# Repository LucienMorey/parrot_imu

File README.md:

# parrot_imu

## Purpose

This design will host an IMU board for the Parody tripedal robotic platform. It will expose connect an IMU to the teensy 4.1 microcontroller with the ability to deliver this data over CAN bus and over an ethernet connection.

## TODOs

### Power Subsystem

Take a 24 V input and reduce it to supplies for powering the associated subsystems.

- [x] 5v supply - tentatitvely [VR10S05](https://www.digikey.com.au/en/products/detail/xp-power/VR10S05/13147713)
- [x] 3.3v supply - tentatitvely [TR05S3V3](https://www.digikey.com.au/en/products/detail/xp-power/TR05S3V3/4488636)
- [x] add terminal to supply power input. probably one of thosegreen terminals that can fit a ferule or a wago terminal [panel mount xt30](https://www.ebay.com.au/itm/393171351901)
- [x] Is it worth bothering with reverse polarity protection? Just a shottkey diode? Nope. just added a gendered connector to prevent this.
- [x] debugging LEDS to indicate presense of power
  - [x] at input line
  - [x] after 5v supply
  - [x] after 3.3V supply
- [x] calculate resitors for power leds

Q. what is an LDO and will it suffice or is a proper dc/dc converter required?

A. They both do the same thing with regard to switching direct current voltages. DC/DC converters are more efficent but more suspetable to noise because they use fets and things that generate switching noise. LDOS are less efficient and will have some current drop depending on the load drawn from the supply. An LDO will work in this scenario and they are cheaper so I will probably go for that. Tony recommended dcdc converter so switching

### Can Transeiver

One potential mechanism for delivering IMU data to the robot comms network. This is the back up option because it cannot interface directly to the ros network. It does not require FD functionality for higher bit rates but this option will be made available if a component can be sourced.

- [x] Pick a can trasniever that can interface with the teensy - picked the [TJA1441AT/0Z](https://www.digikey.com.au/en/products/detail/nxp-usa-inc/TJA1441AT-0Z/13691175). This shouldnt be an issue because it provides both 5v VCC and a seperate VIO input that I can specify the 3.3v logic level required for the teensy
- [x] create footprint and symbol
- [x] add optional termination points
- [x] Add a proper screw terminal or similar mechanism to make adding to the can bus easy [scrw terminal here](https://www.digikey.com.au/en/products/detail/cui-devices/TB005-762-02BE/10064113)
- [ ] Add proper Silk screen markers to indicate CAN-H/L so things are easy

### Ethernet Jack

Intended to be the primary mechanism for delivering imu data to the robot comms network. This is known to beable to interface directly with the ros network through microros on udp transports.

- [x] Find an approppriate RJ45 magjack connector - Currently the [SI-60062-F](https://www.digikey.com.au/en/products/detail/bel-fuse-inc/SI-60062-F/1033372)
- [x] Wire the connector to the teensy. note to follow the schematic outlined on thier magjack page found [here](https://www.pjrc.com/store/ethernet_kit.html). This should be as simple as just adding a capacitor and joining the pins but double check the smc design to be sure.
- [ ] Find link to small pins for ethernet

### Teensy 4.1

Primary microcontroller for interfacing with the IMU.

- [x] obtain premade footprint
- [ ] remember different pin styles for ethernet and general gpio
- [x] spi connection avoiding pin 13 so that ethernet can be used

### IMU

- [x] create symbol
- [x] create footprint
- [x] connect to SPI2 or 3 to avoid collision with ethernet
- [ ] Place footprint of breakout board
- [ ] double check if this should be i2c instead of spi
- [ ] check if interrupt pin or other functionality is going to be helpful

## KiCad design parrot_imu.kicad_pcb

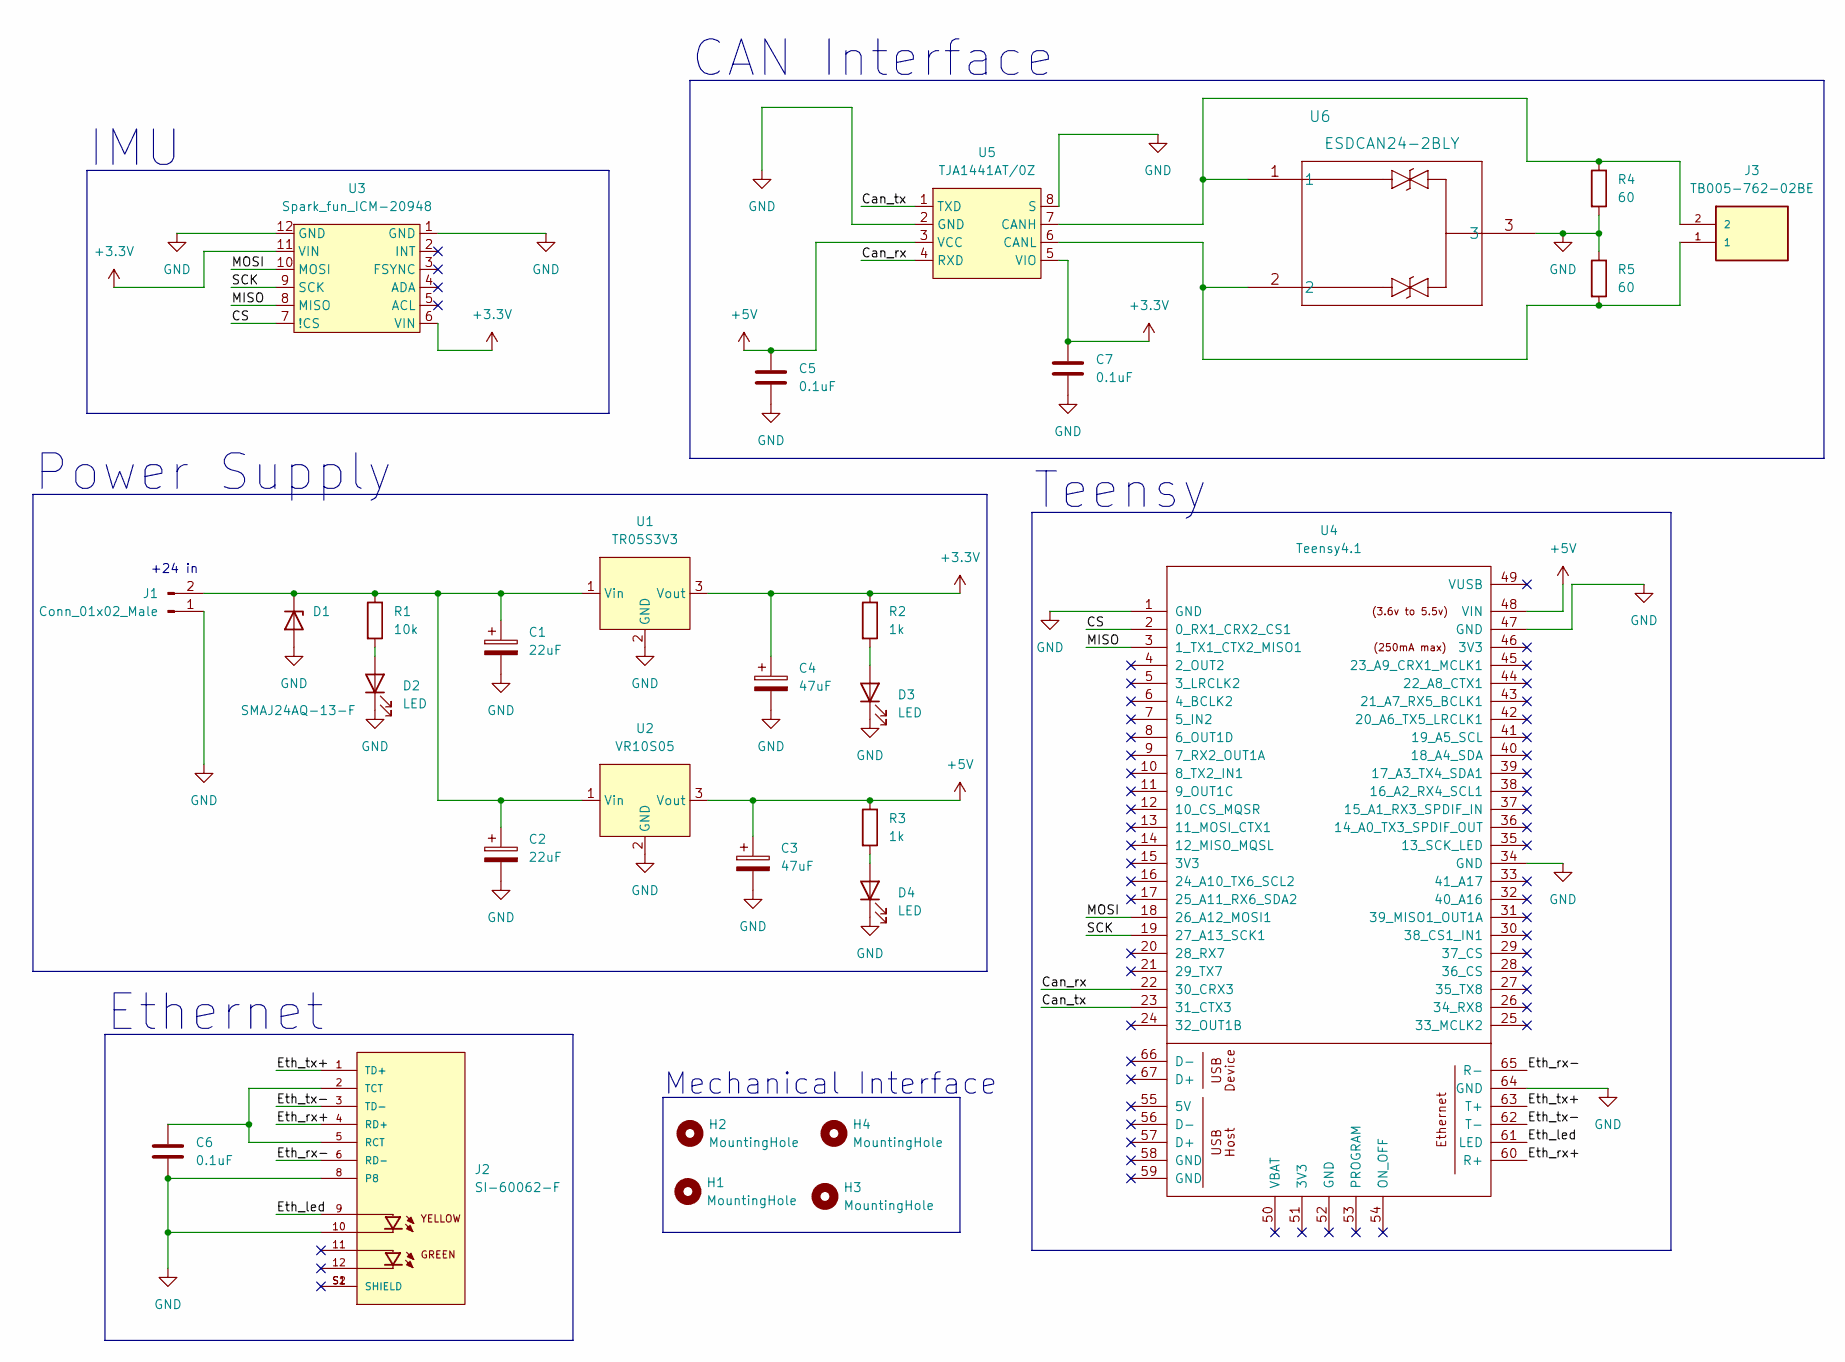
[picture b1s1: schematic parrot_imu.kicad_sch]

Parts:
C1, C2: 22uF; CP_Radial_D5.0mm_P2.00mm; Digikey 732-8857-1-ND
C3, C4: 47uF; CP_Radial_D6.3mm_P2.50mm; Digikey 732-8859-1-ND
C5, C6, C7: 0.1uF; C_0603_1608Metric; Digikey 1276-1935-1-ND
D1: SMAJ24AQ-13-F
D2, D3, D4: LED; LED_0603_1608Metric; Digikey 3147-B1911USD-20D000114U1930CT-ND
H1, H2, H3, H4: MountingHole; MountingHole_3.2mm_M3
J1: Conn_01x02_Male; AMASS_XT30PW-M_1x02_P2.50mm_Horizontal
J2: SI-60062-F; BEL_SI-60062-F; PARTREV B0
J3: TB005-762-02BE; CUI_TB005-762-02BE; Digikey 102-6189-ND
R1: 10k; R_0603_1608Metric; Digikey RNCP0603FTD10K0CT-ND
R2, R3: 1k; R_0603_1608Metric; Digikey RNCP0603FTD1K00CT-ND
R4, R5: 60; R_0603_1608Metric; Digikey 311-60.4HRCT-ND
U1: TR05S3V3; Digikey 1470-2257-5-ND
U2: VR10S05; Digikey 1470-VR10S05-ND
U3: Spark_fun_ICM-20948; Spark_fun_ICM-20498
U4: Teensy4.1; Teensy41
U5: TJA1441AT/0Z; SO-8_3.9x4.9mm_P1.27mm; Digikey 568-TJA1441AT/0ZCT-ND
U6: ESDCAN24-2BLY

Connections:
+3.3V: C4.1, C7.1, R2.1, U1.3 (Vout), U3.6 (VIN), U3.11 (VIN), U5.5 (VIO)
+5V: C3.1, C5.1, R3.1, U2.3 (Vout), U4.48 (VIN), U5.3 (VCC)
/CS: U3.7 (!CS), U4.2 (0_RX1_CRX2_CS1)
/Can_rx: U4.22 (30_CRX3), U5.4 (RXD)
/Can_tx: U4.23 (31_CTX3), U5.1 (TXD)
/Eth_led: J2.9, U4.61 (LED)
/Eth_rx+: J2.4 (RD+), U4.60 (R+)
/Eth_rx-: J2.6 (RD-), U4.65 (R-)
/Eth_tx+: J2.1 (TD+), U4.63 (T+)
/Eth_tx-: J2.3 (TD-), U4.62 (T-)
/MISO: U3.8 (MISO), U4.3 (1_TX1_CTX2_MISO1)
/MOSI: U3.10 (MOSI), U4.18 (26_A12_MOSI1)
/SCK: U3.9 (SCK), U4.19 (27_A13_SCK1)
GND: C1.2, C2.2, C3.2, C4.2, C5.2, C6.2, C7.2, D1.2 (A), D2.1 (K), D3.1 (K), D4.1 (K), J1.1, J2.8, J2.10, R4.2, R5.1, U1.2 (GND), U2.2 (GND), U3.1 (GND), U3.12 (GND), U4.1 (GND), U4.34 (GND), U4.47 (GND), U4.64 (GND), U5.2 (GND), U5.8 (S), U6.3
unnamed: C1.1, C2.1, D1.1 (K), J1.2, R1.1, U1.1 (Vin), U2.1 (Vin)
unnamed: C6.1, J2.2 (TCT), J2.5 (RCT)
unnamed: D2.2 (A), R1.2
unnamed: D3.2 (A), R2.2
unnamed: D4.2 (A), R3.2
unnamed: J3.1, R5.2, U5.6 (CANL), U6.2
unnamed: J3.2, R4.1, U5.7 (CANH), U6.1

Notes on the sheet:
Power Supply
CAN Interface
IMU
Mechanical Interface
Ethernet
Teensy
+24 in

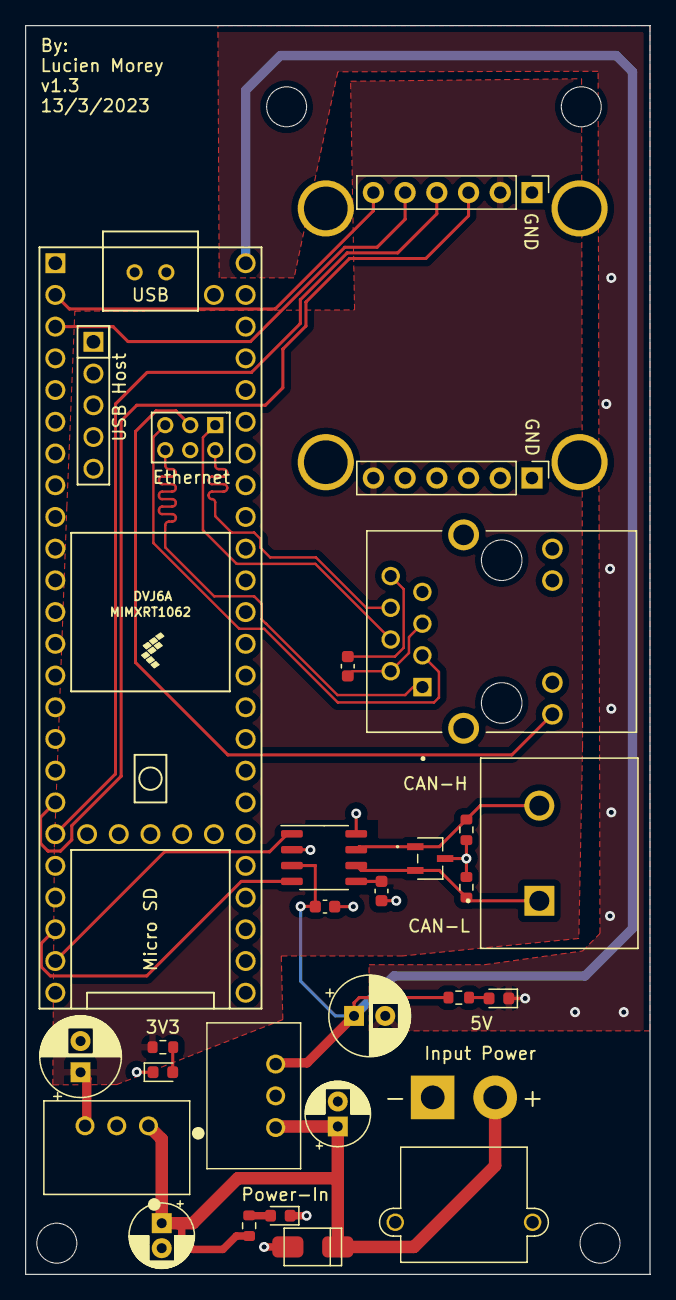
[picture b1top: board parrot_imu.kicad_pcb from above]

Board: 2 copper layers, 50.0 x 100.0 mm, 29 parts (0 on the bottom side), 21 nets.

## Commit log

2023-02-01 created basic kicad project
2023-02-01 added basic notes and todo list for project
2023-02-01 added libraries for teensy
2023-02-01 added teensy to schematic
2023-02-01 added backups folder to gitignore
2023-02-01 added ethernet jack symbol
2023-02-01 added digikey part number to ethernet part
2023-02-01 added readme notes about ethernet comms
2023-02-02 more notes on readme
2023-02-02 created footprint and symbol for ldo
2023-02-02 added additional todos and marked some things as complete
2023-02-03 created symbol and linked footprint for can transciever
2023-02-03 updates to README.md
2023-02-03 tweak to symbols and added imu breakout footprint/symbol
2023-02-03 added ics to schematic
2023-02-03 updates to todo list
2023-02-03 some progress on the schematic and notes on other things to handle
2023-02-06 added connector library
2023-02-06 dcdc supply footprints and symbols
2023-02-06 schematic done pre review
2023-02-06 added notes and digikey part numbers
2023-02-06 README updates
2023-02-06 design review with tony
2023-02-08 added tvs diodes to schematic
2023-02-08 switched to xt30 connector and added leds for power
2023-02-08 update to readme
2023-02-08 filled in footprints and digikey id for most parts
2023-02-08 readme update
2023-02-22 added missing footprint for can protection and imported parts to pcb design
2023-02-22 sort out errors with footprints and add mounting holes
2023-02-22 start of laying out components
2023-02-22 most of pcb and some steps
2023-02-22 completed draft pcb and added model for imu
2023-02-22 fix unconnected plane error
2023-02-22 fix errors with unconnected components
2023-02-23 removed trace between shield on ethernet
2023-02-23 dump of progress
2023-02-23 pcb redesign
2023-02-26 added step file for ethernet
2023-02-26 readded xt30 step model
2023-02-26 silk screen stuff
2023-02-27 add tony fixes from design review
2023-05-18 update pcb
2024-09-07 collapse code from other repo into this one

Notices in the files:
parts and their libraries:
Copyright 2021 Accelerated Designs. All rights reserved.
